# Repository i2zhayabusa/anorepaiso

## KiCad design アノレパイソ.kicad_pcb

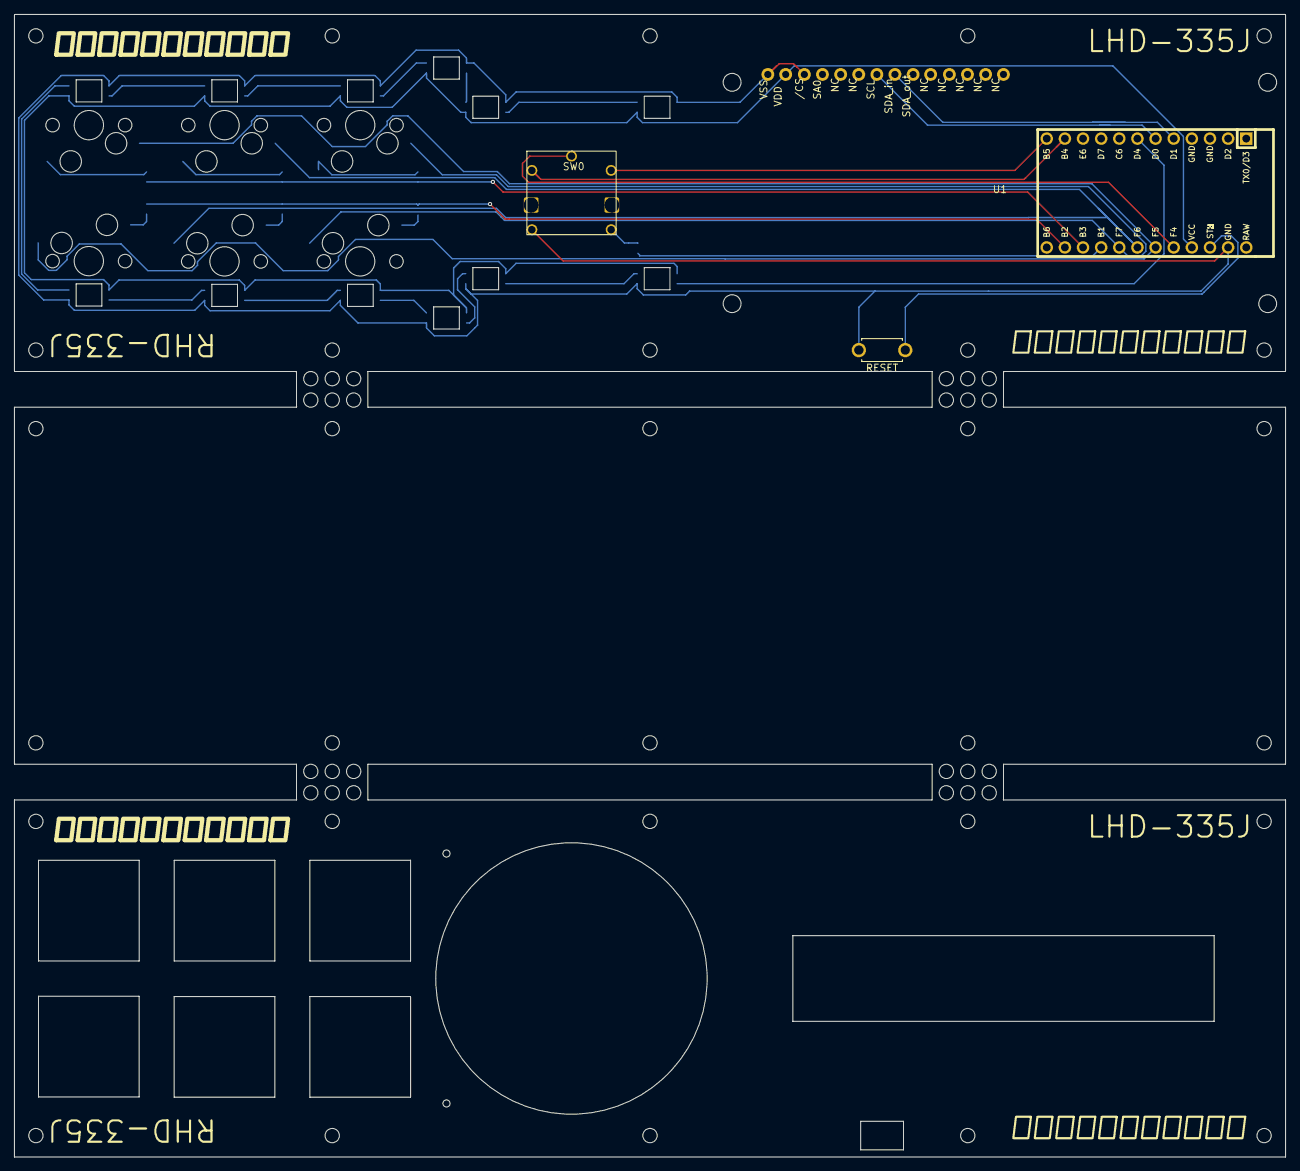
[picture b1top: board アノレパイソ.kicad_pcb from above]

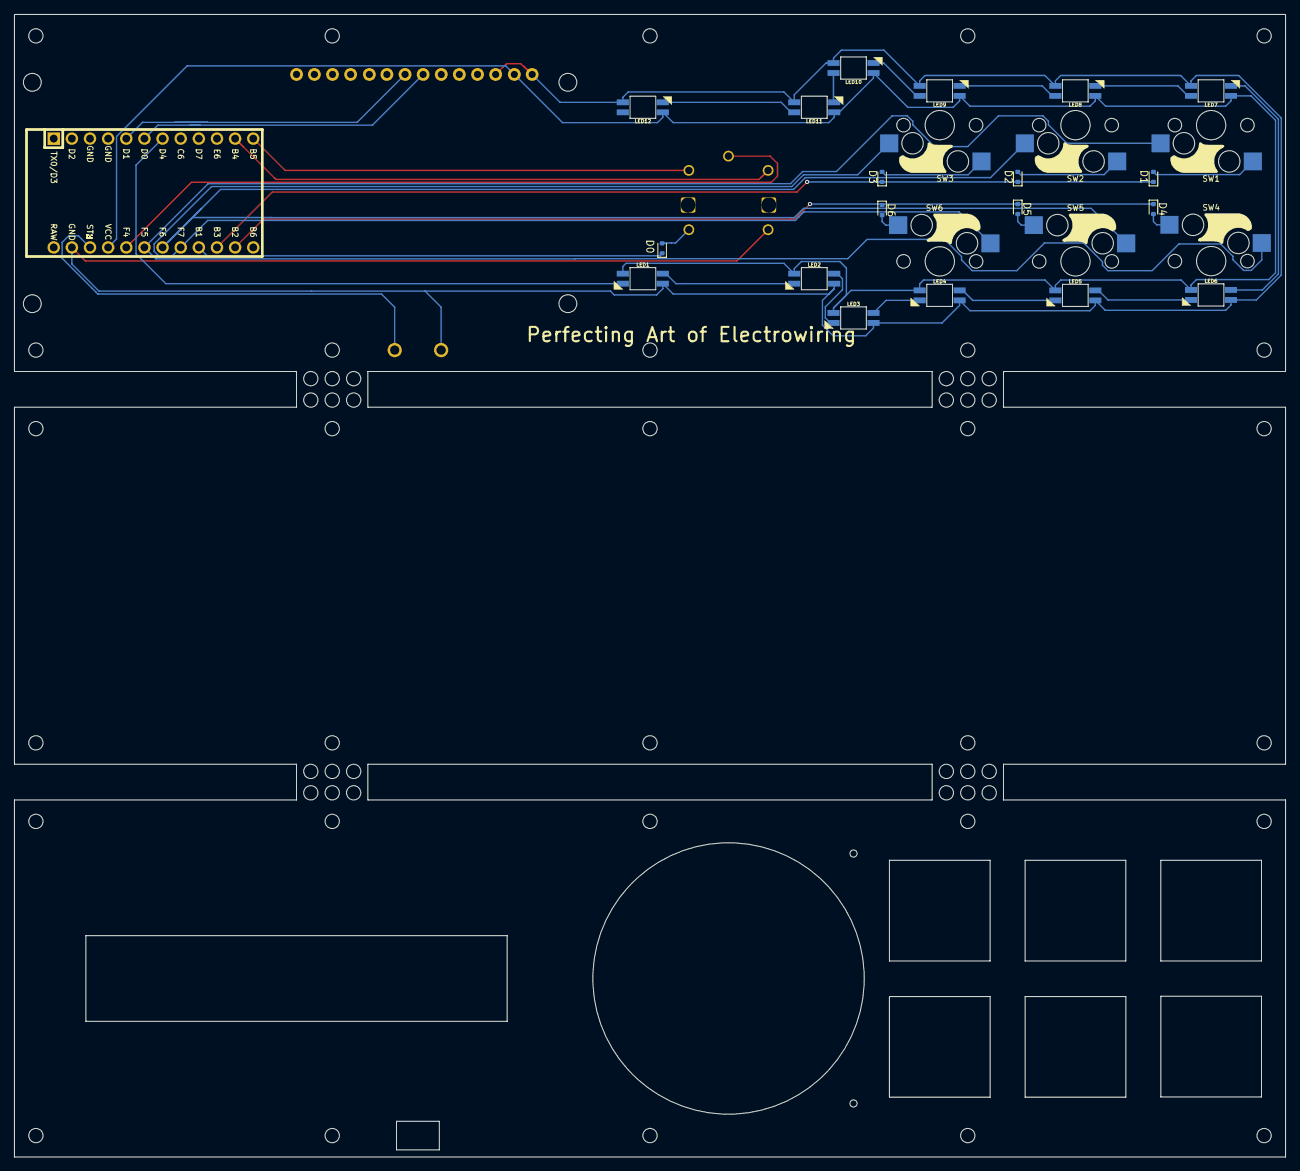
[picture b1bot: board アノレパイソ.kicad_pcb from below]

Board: 2 copper layers, 178.0 x 160.0 mm, 35 parts (31 on the bottom side), 33 nets.

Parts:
D0, D1, D2, D3, D4, D5, D6: 1N4148WT; D_SOD-523
LED1, LED2, LED3, LED4, LED5, LED6, LED7, LED8, LED9, LED10, LED11, LED12: LED_SK6812MINI-E; YS-SK6812MINI-E
SW0: RotaryEncoder_Switch; EC12D1524406
SW1, SW2#2, SW3, SW4#2, SW5#2, SW6: SW_PUSH; keyswitch_cherrymx_hotswap_1u
SW1#2, SW2, SW3#2, SW4, SW5, SW6#2: SW_PUSH; SW_Hole_1u
SW9: SW_PUSH; ResetSW
U1: SO1602AWWB-UC-WB-U
U3: ProMicro; ArduinoProMicro

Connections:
Col0: SW0.S2, U3.20 (F4/A3)
Col1: SW1.1, SW4#2.1, U3.19 (F5/A2)
Col2: SW2#2.1, SW5#2.1, U3.18 (F6/A1)
Col3: SW3.1, SW6.1, U3.17 (F7/A0)
GND: LED1.2 (VSS), LED2.2 (VSS), LED3.2 (VSS), LED4.2 (VSS), LED5.2 (VSS), LED6.2 (VSS), LED7.2 (VSS), LED8.2 (VSS), LED9.2 (VSS), LED10.2 (VSS), LED11.2 (VSS), LED12.2 (VSS), SW0.C, SW9.2, U1.1 (VSS), U1.3 (/CS), U3.23 (GND)
LED: LED1.3 (DIN), U3.7 (4/D4)
unnamed: D0.2 (A), SW0.S1
unnamed: D1.2 (A), SW1.2
unnamed: D2.2 (A), SW2#2.2
unnamed: D3.2 (A), SW3.2
unnamed: D4.2 (A), SW4#2.2
unnamed: D5.2 (A), SW5#2.2
unnamed: D6.2 (A), SW6.2
unnamed: LED1.1 (DOUT), LED2.3 (DIN)
unnamed: LED2.1 (DOUT), LED3.3 (DIN)
unnamed: LED3.1 (DOUT), LED4.3 (DIN)
unnamed: LED4.1 (DOUT), LED5.3 (DIN)
unnamed: LED5.1 (DOUT), LED6.3 (DIN)
unnamed: LED6.1 (DOUT), LED7.3 (DIN)
unnamed: LED7.1 (DOUT), LED8.3 (DIN)
unnamed: LED8.1 (DOUT), LED9.3 (DIN)
unnamed: LED9.1 (DOUT), LED10.3 (DIN)
unnamed: LED10.1 (DOUT), LED11.3 (DIN)
unnamed: LED11.1 (DOUT), LED12.3 (DIN)
RE_A: SW0.A, U3.11 (8/B4)
RE_B: SW0.B, U3.12 (9/B5)
Reset: SW9.1, U3.22 (RST)
Row0: D0.1 (K), U3.16 (B1/15)
Row1: D1.1 (K), D2.1 (K), D3.1 (K), U3.15 (B3/14)
Row2: D4.1 (K), D5.1 (K), D6.1 (K), U3.14 (B2/16)
SCL: U1.7 (SCL), U3.6 (3/D0/SCL)
SDA: U1.8 (SDAin), U3.5 (2/D1/SDA)
VCC: LED1.4 (VDD), LED2.4 (VDD), LED3.4 (VDD), LED4.4 (VDD), LED5.4 (VDD), LED6.4 (VDD), LED7.4 (VDD), LED8.4 (VDD), LED9.4 (VDD), LED10.4 (VDD), LED11.4 (VDD), LED12.4 (VDD), U1.2 (VDD), U3.21 (VCC)

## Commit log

2025-01-22 回路図を作りきったところまで
2025-01-25 PCBエディタで可能な限り部品の配置と配線を実施
2025-01-26 μCOMを残して配線完了。
2025-01-29 いったん今の知識でやれることは全部終わり。赤ペン待ち。
2025-02-01 電気系のエラーはすべてなくした。
2025-02-05 2/5(水)定例MTG指摘対策版
2025-02-11 前夜祭更新
2025-02-12 基板で暫定表面・裏面を作った。
2025-02-13 鶴野さん出社最終日前に更新。
